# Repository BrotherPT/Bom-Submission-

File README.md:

# Tic-Tac-Toe game

This project consists of a small Tic-Tac-Toe game, it uses individual adressable RGB'S,buttons and 328pb as the chip. The schematic and board design were done using Eagle.

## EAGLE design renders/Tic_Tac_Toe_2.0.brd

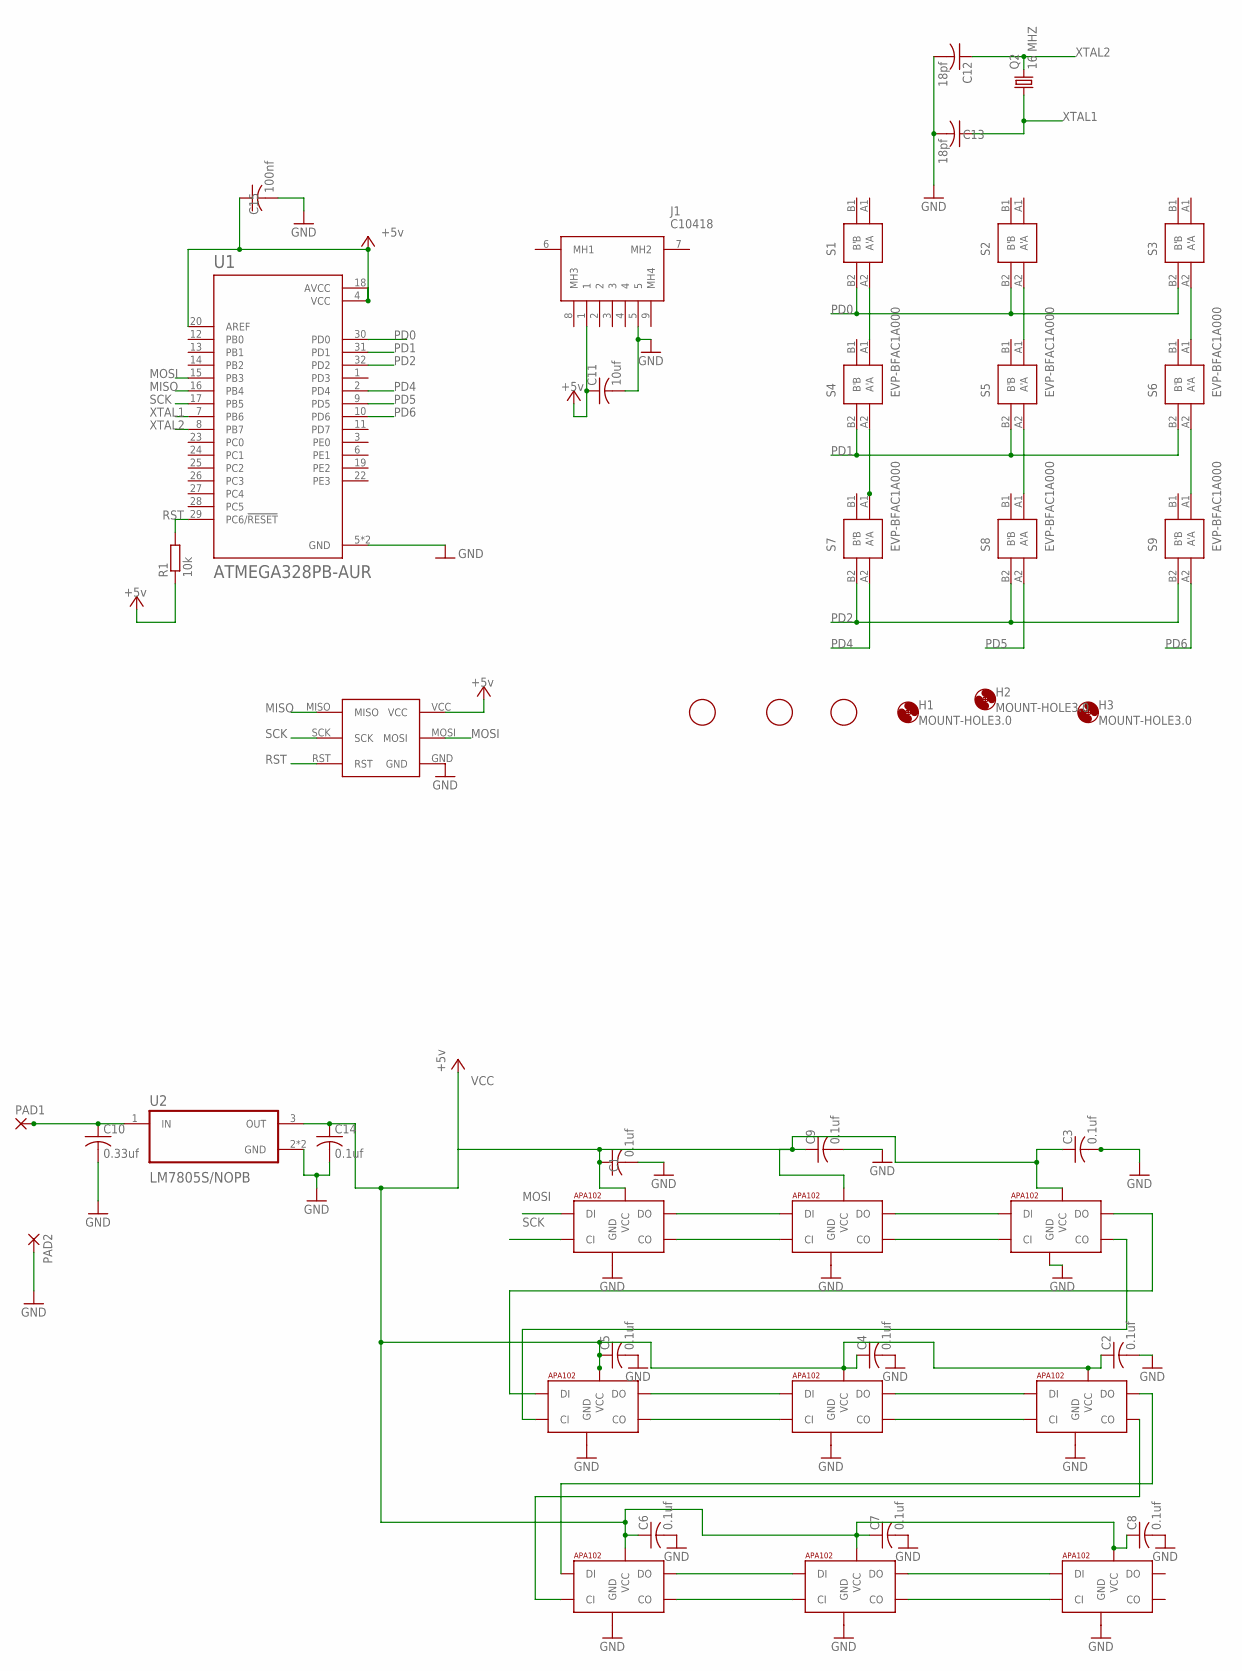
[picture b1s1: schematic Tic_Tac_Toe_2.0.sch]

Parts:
C1, C2, C3, C4, C5, C6, C7, C8, C9, C14: 0.1uf; C0805
C10: 0.33uf; C0805
C11: 10uf; C0805
C12, C13: 18pf; C0805
C15: 100nf; C0805
H1, H2, H3: MOUNT-HOLE3.0; 3,0
J1: C10418
PAD1, PAD2: 2,15/1,0
Q2: 16 MHZ; HC49UP
R1: 10k; M0805
S1, S2, S3, S4, S5, S6, S7, S8, S9: EVP-BFAC1A000; EVPBFAC1A000
U1: ATMEGA328PB-AUR; QFP80P900X900X120-32N
U2: LM7805S/NOPB; TO254P1524X483-4N
U$1: AVR-ISP
U$2, U$3, U$4, U$5, U$6, U$7, U$8, U$9, U$10: APA1025050; APA102_5050
U$11, U$12, U$13: FIDUCIAL; FIDUCIAL_1MM

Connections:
GND: C1.2, C2.2, C3.2, C4.2, C5.2, C6.2, C7.2, C8.2, C9.2, C10.2, C11.2, C12.2, C13.2, C14.2, C15.2, J1.5, PAD2.1, U1.5 (GND), U1.21 (GND), U2.2 (GND), U2.4 (GND), U$1.GND, U$2.6 (GND), U$3.6 (GND), U$4.6 (GND), U$5.6 (GND), U$6.6 (GND), U$7.6 (GND), U$8.6 (GND), U$9.6 (GND), U$10.6 (GND)
MISO: U1.16 (PB4), U$1.MISO
MOSI: U1.15 (PB3), U$1.MOSI, U$2.4 (DI)
unnamed: C10.1, PAD1.1, U2.1 (IN)
unnamed: U$2.3 (DO), U$3.4 (DI)
unnamed: U$2.2 (CO), U$3.5 (CI)
unnamed: U$3.3 (DO), U$4.4 (DI)
unnamed: U$3.2 (CO), U$4.5 (CI)
unnamed: U$8.3 (DO), U$9.4 (DI)
unnamed: S1.A2 (A'), S4.A1 (A)
unnamed: S6.A2 (A'), S9.A1 (A)
unnamed: S4.A2 (A'), S7.A1 (A)
unnamed: S2.A2 (A'), S5.A1 (A)
unnamed: S5.A2 (A'), S8.A1 (A)
unnamed: S3.A2 (A'), S6.A1 (A)
unnamed: U$4.3 (DO), U$5.4 (DI)
unnamed: U$4.2 (CO), U$5.5 (CI)
unnamed: U$5.3 (DO), U$6.4 (DI)
unnamed: U$5.2 (CO), U$6.5 (CI)
unnamed: U$6.3 (DO), U$7.4 (DI)
unnamed: U$6.2 (CO), U$7.5 (CI)
unnamed: U$8.2 (CO), U$9.5 (CI)
unnamed: U$9.3 (DO), U$10.4 (DI)
unnamed: U$9.2 (CO), U$10.5 (CI)
unnamed: U$7.2 (CO), U$8.5 (CI)
unnamed: U$7.3 (DO), U$8.4 (DI)
PD0: S1.B2 (B'), S2.B2 (B'), S3.B2 (B'), U1.30 (PD0)
PD1: S4.B2 (B'), S5.B2 (B'), S6.B2 (B'), U1.31 (PD1)
PD2: S7.B2 (B'), S8.B2 (B'), S9.B2 (B'), U1.32 (PD2)
PD4: S7.A2 (A'), U1.2 (PD4)
PD5: S8.A2 (A'), U1.9 (PD5)
PD6: S9.A2 (A'), U1.10 (PD6)
RST: R1.2, U1.29 (PC6/!RESET), U$1.RST
SCK: U1.17 (PB5), U$1.SCK, U$2.5 (CI)
VCC: C1.1, C2.1, C3.1, C4.1, C5.1, C6.1, C7.1, C8.1, C9.1, C11.1, C14.1, C15.1, J1.1, R1.1, U1.4 (VCC), U1.18 (AVCC), U1.20 (AREF), U2.3 (OUT), U$1.VCC, U$2.1 (VCC), U$3.1 (VCC), U$4.1 (VCC), U$5.1 (VCC), U$6.1 (VCC), U$7.1 (VCC), U$8.1 (VCC), U$9.1 (VCC), U$10.1 (VCC)
XTAL1: C13.1, Q2.1, U1.7 (PB6)
XTAL2: C12.1, Q2.2, U1.8 (PB7)

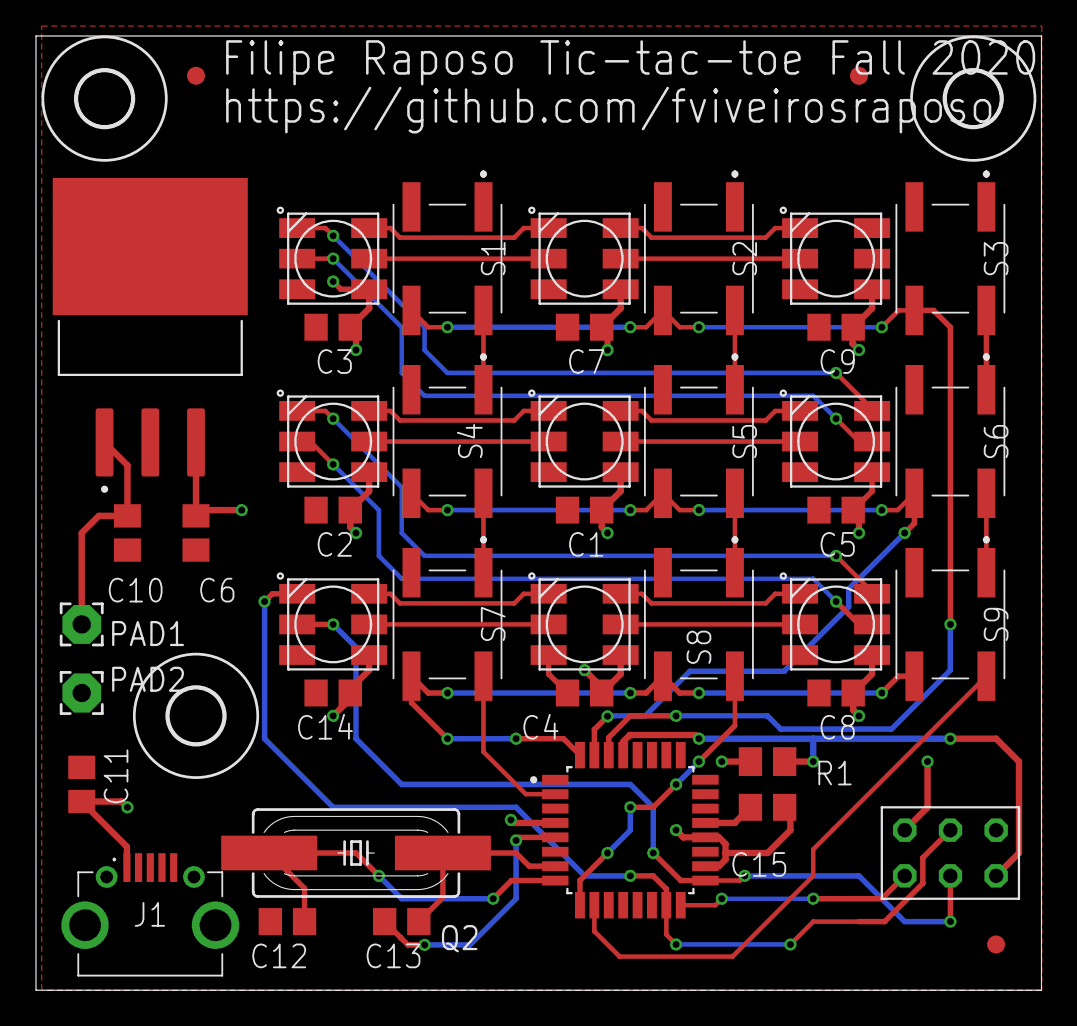
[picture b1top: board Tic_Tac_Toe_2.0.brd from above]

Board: 2 copper layers, 55.9 x 53.0 mm, 47 parts (0 on the bottom side), 37 nets.

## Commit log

2020-11-11 upodate
